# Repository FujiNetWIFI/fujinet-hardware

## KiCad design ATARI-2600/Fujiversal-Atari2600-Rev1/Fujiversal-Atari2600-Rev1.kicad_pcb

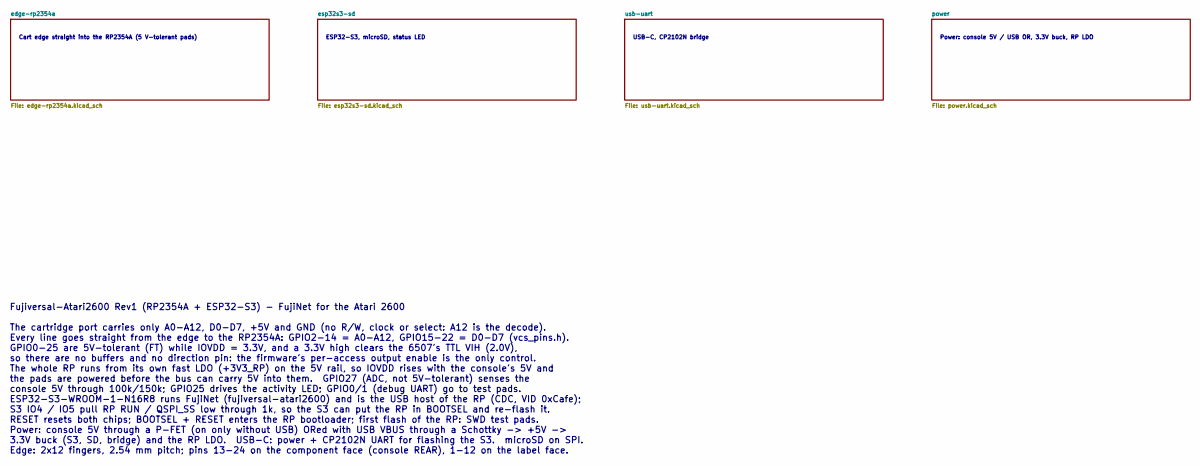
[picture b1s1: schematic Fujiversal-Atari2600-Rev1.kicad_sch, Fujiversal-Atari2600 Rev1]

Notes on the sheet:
Cart edge straight into the RP2354A (5 V-tolerant pads)
ESP32-S3, microSD, status LED
USB-C, CP2102N bridge
Power: console 5V / USB OR, 3.3V buck, RP LDO
Fujiversal-Atari2600 Rev1 (RP2354A + ESP32-S3) - FujiNet for the Atari 2600 The cartridge port carries only A0-A12, D0-D7, +5V and GND (no R/W, clock or select: A12 is the decode). Every line goes straight from the edge to the RP2354A: GPIO2-14 = A0-A12, GPIO15-22 = D0-D7 (vcs_pins.h). GPIO0-25 are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

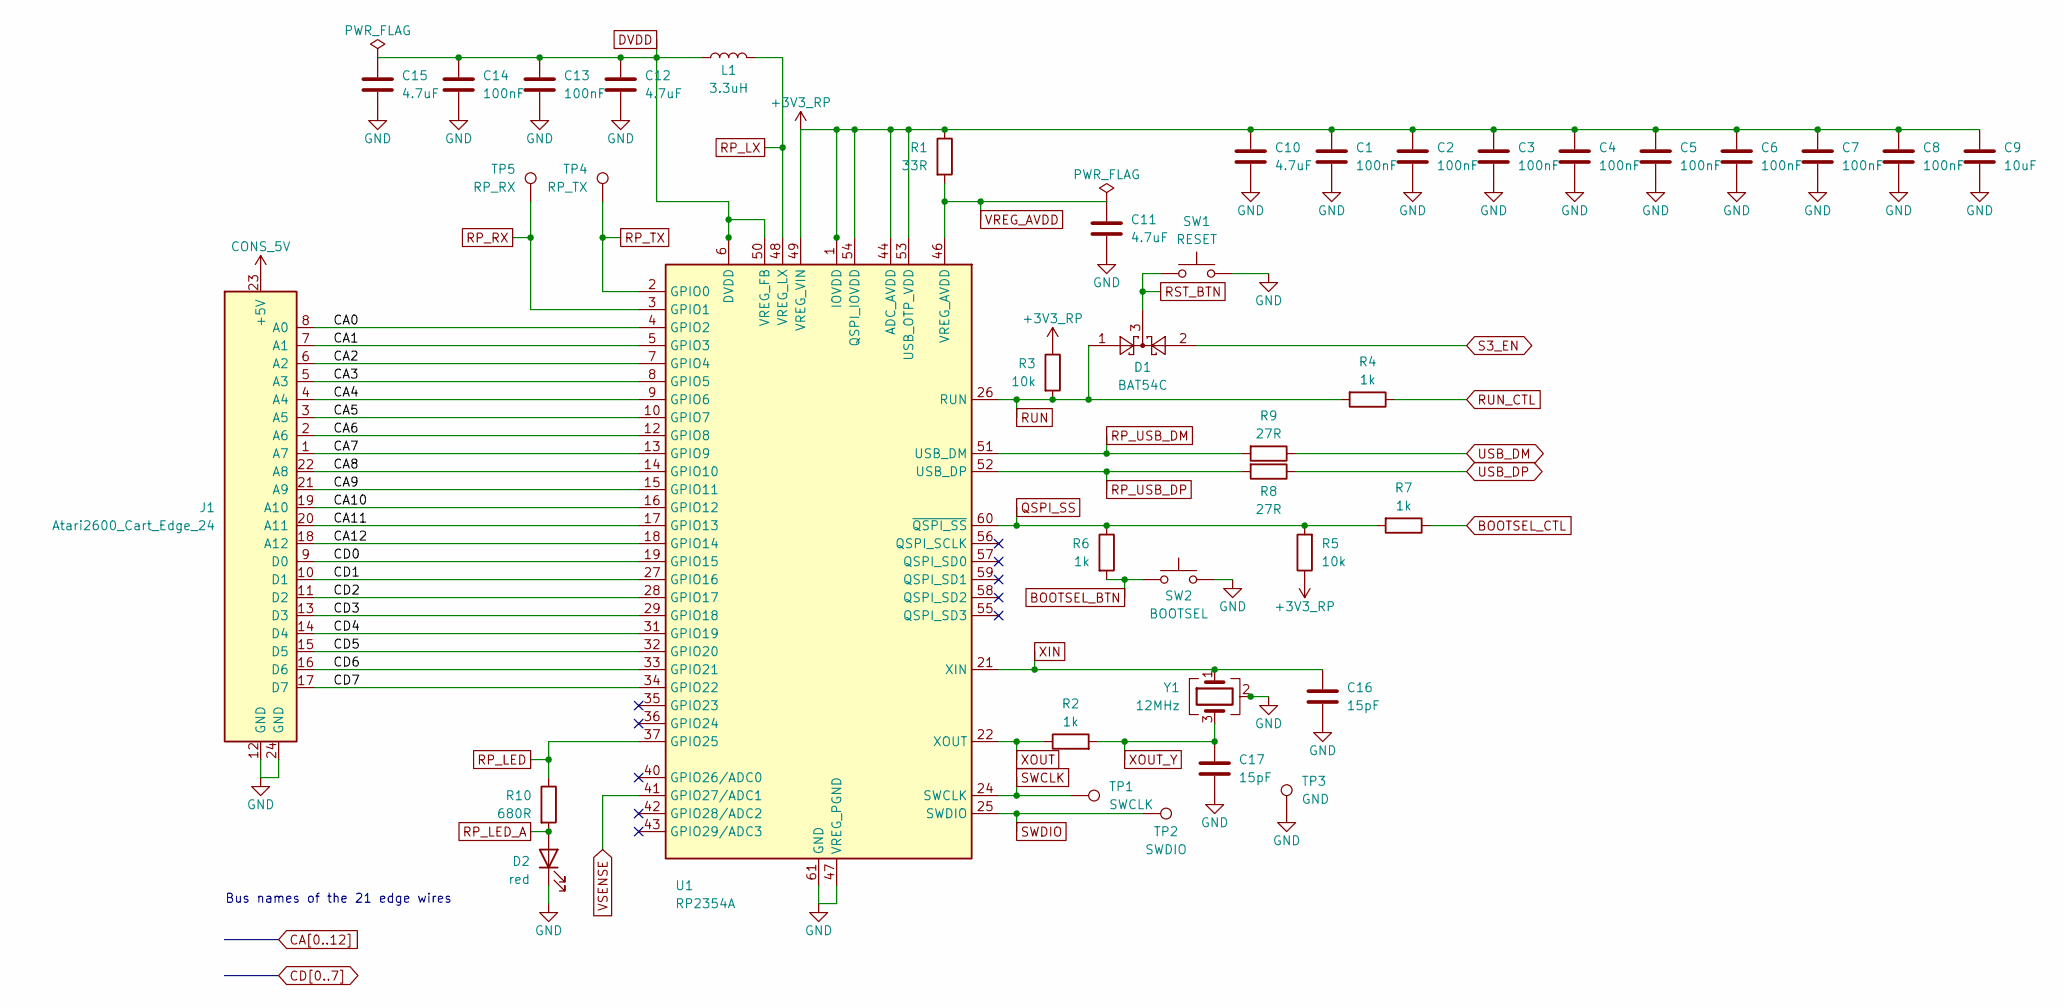
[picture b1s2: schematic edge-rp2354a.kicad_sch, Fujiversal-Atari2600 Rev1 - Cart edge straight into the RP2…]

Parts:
C1, C2, C3, C4, C5, C6, C7, C13, C14: 100nF; C_0603_1608Metric; MPN CC0603KRX7R9BB104; LCSC C14663
C8: 100nF; RPI_C0402; MPN CL05B104KO5NNNC; LCSC C1525
C9: 10uF; C_0603_1608Metric; MPN CL10A106KP8NNNC; LCSC C19702
C10, C12: 4.7uF; RPI_C0402_wide; MPN CL05A475MP5NRNC; LCSC C23733
C11: 4.7uF; RPI_C0402; MPN CL05A475MP5NRNC; LCSC C23733
C15: 4.7uF; C_0603_1608Metric; MPN CL10A475KO8NNNC; LCSC C19666
C16, C17: 15pF; C_0603_1608Metric; MPN CL10C150JB8NNNC; LCSC C1644
D1: BAT54C; SOT-23; MPN BAT54C,215; LCSC C37704
D2: red; LED_0603_1608Metric; MPN KT-0603R; LCSC C2286
J1: Atari2600_Cart_Edge_24
L1: 3.3uH; RPI_L_AOTA-B201610S3R3; MPN AOTA-B201610S3R3-101-T; LCSC C42411119
R1: 33R; RPI_R0402; MPN 0402WGF330JTCE; LCSC C25105
R2, R4, R6, R7: 1k; R_0603_1608Metric; MPN 0603WAF1001T5E; LCSC C21190
R3, R5: 10k; R_0603_1608Metric; MPN 0603WAF1002T5E; LCSC C25804
R8, R9: 27R; RPI_R0402; MPN 0402WGF270JTCE; LCSC C25100
R10: 680R; R_0603_1608Metric; MPN 0603WAF6800T5E; LCSC C23228
SW1: RESET; SW_SPST_TL3342; MPN TL3342F160QG; LCSC C2886898
SW2: BOOTSEL; SW_SPST_TL3342; MPN TL3342F160QG; LCSC C2886898
TP1: SWCLK; TestPoint_Pad_D1.5mm
TP2: SWDIO; TestPoint_Pad_D1.5mm
TP3: GND; TestPoint_Pad_D1.5mm
TP4: RP_TX; TestPoint_Pad_D1.5mm
TP5: RP_RX; TestPoint_Pad_D1.5mm
U1: RP2354A; RPI_RP2350A_QFN60; MPN RP2354A; LCSC C41378174
Y1: 12MHz; Crystal_SMD_3225-4Pin_3.2x2.5mm; MPN ABM8-272-T3; LCSC C20625731

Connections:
+3V3_RP: C1.1, C2.1, C3.1, C4.1, C5.1, C6.1, C7.1, C8.1, C9.1, C10.1, R1.1, R3.1, R5.1, U1.1 (IOVDD), U1.11 (IOVDD), U1.20 (IOVDD), U1.30 (IOVDD), U1.38 (IOVDD), U1.44 (ADC_AVDD), U1.45 (IOVDD), U1.49 (VREG_VIN), U1.53 (USB_OTP_VDD), U1.54 (QSPI_IOVDD); also elsewhere on the board
BOOTSEL_BTN: R6.2, SW2.1
BOOTSEL_CTL: R7.1; also elsewhere on the board
CA0: J1.8 (A0), U1.4 (GPIO2)
CA1: J1.7 (A1), U1.5 (GPIO3)
CA2: J1.6 (A2), U1.7 (GPIO4)
CA3: J1.5 (A3), U1.8 (GPIO5)
CA4: J1.4 (A4), U1.9 (GPIO6)
CA5: J1.3 (A5), U1.10 (GPIO7)
CA6: J1.2 (A6), U1.12 (GPIO8)
CA7: J1.1 (A7), U1.13 (GPIO9)
CA8: J1.22 (A8), U1.14 (GPIO10)
CA9: J1.21 (A9), U1.15 (GPIO11)
CA10: J1.19 (A10), U1.16 (GPIO12)
CA11: J1.20 (A11), U1.17 (GPIO13)
CA12: J1.18 (A12), U1.18 (GPIO14)
CD0: J1.9 (D0), U1.19 (GPIO15)
CD1: J1.10 (D1), U1.27 (GPIO16)
CD2: J1.11 (D2), U1.28 (GPIO17)
CD3: J1.13 (D3), U1.29 (GPIO18)
CD4: J1.14 (D4), U1.31 (GPIO19)
CD5: J1.15 (D5), U1.32 (GPIO20)
CD6: J1.16 (D6), U1.33 (GPIO21)
CD7: J1.17 (D7), U1.34 (GPIO22)
CONS_5V: J1.23 (+5V); also elsewhere on the board
DVDD: C12.1, C13.1, C14.1, C15.1, L1.1, U1.6 (DVDD), U1.23 (DVDD), U1.39 (DVDD), U1.50 (VREG_FB)
GND: C1.2, C2.2, C3.2, C4.2, C5.2, C6.2, C7.2, C8.2, C9.2, C10.2, C11.2, C12.2, C13.2, C14.2, C15.2, C16.2, C17.2, D2.1 (K), J1.12 (GND), J1.24 (GND), SW1.2, SW2.2, TP3.1, U1.47 (VREG_PGND), U1.61 (GND), Y1.2 (G), Y1.4 (G); also elsewhere on the board
QSPI_SS: R5.2, R6.1, R7.2, U1.60 (~QSPI_SS)
RP_LED: R10.1, U1.37 (GPIO25)
RP_LED_A: D2.2 (A), R10.2
RP_LX: L1.2, U1.48 (VREG_LX)
RP_RX: TP5.1, U1.3 (GPIO1)
RP_TX: TP4.1, U1.2 (GPIO0)
RP_USB_DM: R9.2, U1.51 (USB_DM)
RP_USB_DP: R8.2, U1.52 (USB_DP)
RST_BTN: D1.3, SW1.1
RUN: D1.1, R3.2, R4.2, U1.26 (RUN)
RUN_CTL: R4.1; also elsewhere on the board
S3_EN: D1.2; also elsewhere on the board
SWCLK: TP1.1, U1.24 (SWCLK)
SWDIO: TP2.1, U1.25 (SWDIO)
USB_DM: R9.1; also elsewhere on the board
USB_DP: R8.1; also elsewhere on the board
VREG_AVDD: C11.1, R1.2, U1.46 (VREG_AVDD)
VSENSE: U1.41 (GPIO27/ADC1); also elsewhere on the board
XIN: C16.1, U1.21 (XIN), Y1.1
XOUT: R2.1, U1.22 (XOUT)
XOUT_Y: C17.1, R2.2, Y1.3

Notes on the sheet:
Bus names of the 21 edge wires

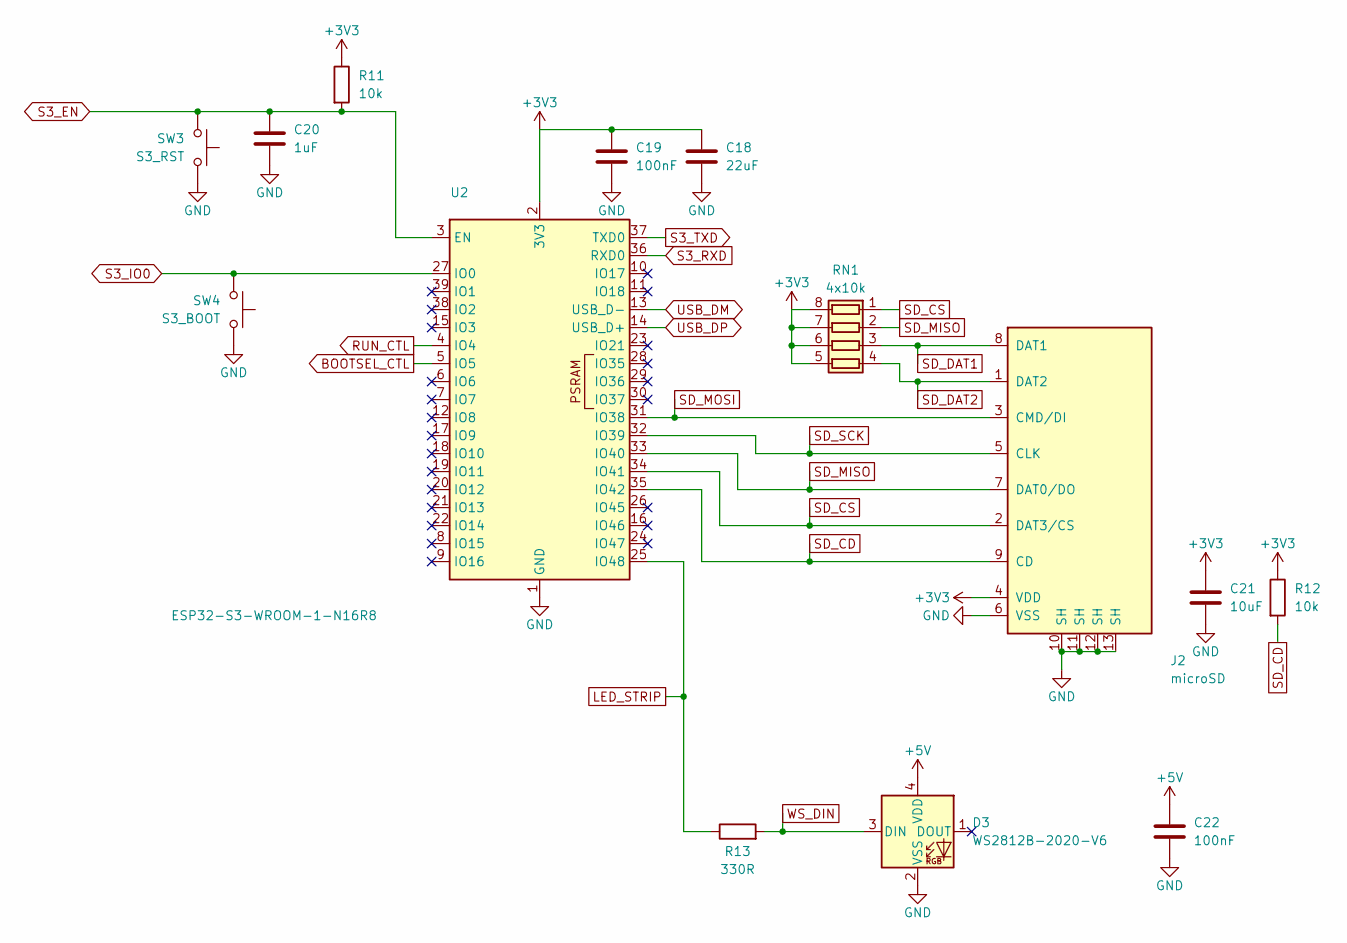
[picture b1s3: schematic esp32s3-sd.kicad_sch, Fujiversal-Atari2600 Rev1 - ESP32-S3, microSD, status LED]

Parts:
C18: 22uF; C_0805_2012Metric; MPN CL21A226MAQNNNE; LCSC C45783
C19, C22: 100nF; C_0603_1608Metric; MPN CC0603KRX7R9BB104; LCSC C14663
C20: 1uF; C_0603_1608Metric; MPN CL10A105KB8NNNC; LCSC C15849
C21: 10uF; C_0603_1608Metric; MPN CL10A106KP8NNNC; LCSC C19702
D3: WS2812B-2020-V6; LED_WS2812B-2020_PLCC4_2.0x2.0mm; MPN WS2812B-2020-V6; LCSC C52917434
J2: microSD; TF-SMD_TF-015; MPN TF-015; LCSC C113206
R11, R12: 10k; R_0603_1608Metric; MPN 0603WAF1002T5E; LCSC C25804
R13: 330R; R_0603_1608Metric; MPN 0603WAF3300T5E; LCSC C23138
RN1: 4x10k; R_Array_Convex_4x0603; MPN 4D03WGJ0103T5E; LCSC C29718
SW3: S3_RST; SW_SPST_TL3342; MPN TL3342F160QG; LCSC C2886898
SW4: S3_BOOT; SW_SPST_TL3342; MPN TL3342F160QG; LCSC C2886898
U2: ESP32-S3-WROOM-1-N16R8; ESP32-S3-WROOM-1; MPN ESP32-S3-WROOM-1-N16R8; LCSC C2913202

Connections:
+3V3: C18.1, C19.1, C21.1, J2.4 (VDD), R11.1, R12.1, RN1.5 (R4.2), RN1.6 (R3.2), RN1.7 (R2.2), RN1.8 (R1.2), U2.2 (3V3); also elsewhere on the board
+5V: C22.1, D3.4 (VDD); also elsewhere on the board
BOOTSEL_CTL: U2.5 (IO5); also elsewhere on the board
GND: C18.2, C19.2, C20.2, C21.2, C22.2, D3.2 (VSS), J2.6 (VSS), J2.10 (SH), J2.11 (SH), J2.12 (SH), J2.13 (SH), SW3.2, SW4.2, U2.1 (GND), U2.40 (GND), U2.41 (GND); also elsewhere on the board
LED_STRIP: R13.1, U2.25 (IO48)
RUN_CTL: U2.4 (IO4); also elsewhere on the board
S3_EN: C20.1, R11.2, SW3.1, U2.3 (EN); also elsewhere on the board
S3_IO0: SW4.1, U2.27 (IO0); also elsewhere on the board
S3_RXD: U2.36 (RXD0); also elsewhere on the board
S3_TXD: U2.37 (TXD0); also elsewhere on the board
SD_CD: J2.9 (CD), R12.2, U2.35 (IO42)
SD_CS: J2.2 (DAT3/CS), RN1.1 (R1.1), U2.34 (IO41)
SD_DAT1: J2.8 (DAT1), RN1.3 (R3.1)
SD_DAT2: J2.1 (DAT2), RN1.4 (R4.1)
SD_MISO: J2.7 (DAT0/DO), RN1.2 (R2.1), U2.33 (IO40)
SD_MOSI: J2.3 (CMD/DI), U2.31 (IO38)
SD_SCK: J2.5 (CLK), U2.32 (IO39)
USB_DM: U2.13 (USB_D-); also elsewhere on the board
USB_DP: U2.14 (USB_D+); also elsewhere on the board
WS_DIN: D3.3 (DIN), R13.2

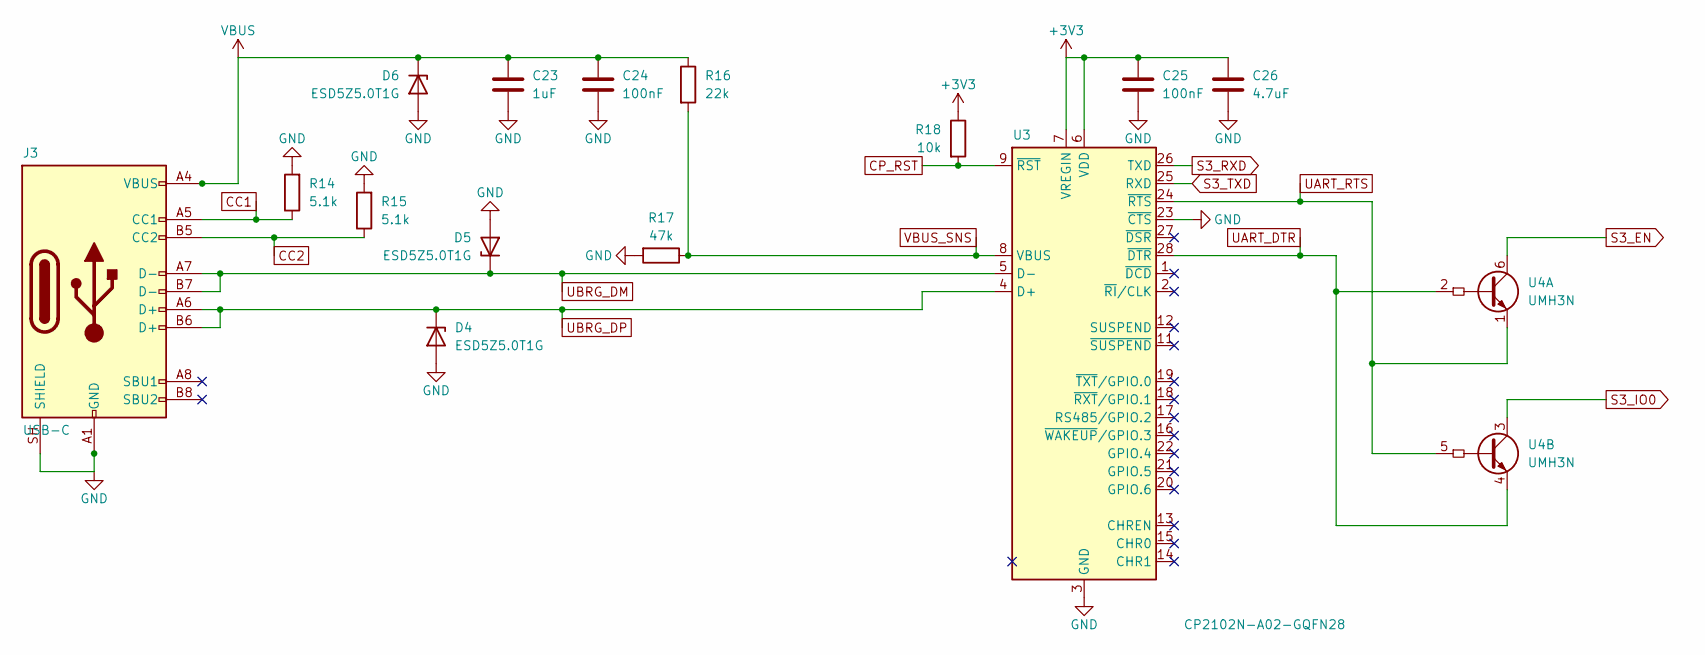
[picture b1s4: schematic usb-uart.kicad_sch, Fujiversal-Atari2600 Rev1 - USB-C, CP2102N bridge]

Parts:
C23: 1uF; C_0603_1608Metric; MPN CL10A105KB8NNNC; LCSC C15849
C24, C25: 100nF; C_0603_1608Metric; MPN CC0603KRX7R9BB104; LCSC C14663
C26: 4.7uF; C_0603_1608Metric; MPN CL10A475KO8NNNC; LCSC C19666
D4, D5, D6: ESD5Z5.0T1G; D_SOD-523; MPN ESD5Z5.0T1G; LCSC C82044
J3: USB-C; USB_C_Receptacle_HRO_TYPE-C-31-M-12; MPN TYPE-C-31-M-12; LCSC C165948
R14, R15: 5.1k; R_0603_1608Metric; MPN 0603WAF5101T5E; LCSC C23186
R16: 22k; R_0603_1608Metric; MPN 0603WAF2202T5E; LCSC C31850
R17: 47k; R_0603_1608Metric; MPN 0603WAF4702T5E; LCSC C25819
R18: 10k; R_0603_1608Metric; MPN 0603WAF1002T5E; LCSC C25804
U3: CP2102N-A02-GQFN28; QFN-28-1EP_5x5mm_P0.5mm_EP3.35x3.35mm; MPN CP2102N-A02-GQFN28R; LCSC C964632
U4: UMH3N; SOT-363_SC-70-6; MPN UMH3N; LCSC C62892

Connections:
+3V3: C25.1, C26.1, R18.1, U3.6 (VDD), U3.7 (VREGIN); also elsewhere on the board
CC1: J3.A5 (CC1), R14.1
CC2: J3.B5 (CC2), R15.1
CP_RST: R18.2, U3.9 (~RST)
GND: C23.2, C24.2, C25.2, C26.2, D4.2 (A), D5.2 (A), D6.2 (A), J3.A1 (GND), J3.A12 (GND), J3.B1 (GND), J3.B12 (GND), J3.SH (SHIELD), R14.2, R15.2, R17.2, U3.3 (GND), U3.23 (~CTS), U3.29 (GND); also elsewhere on the board
S3_EN: U4.6 (C1); also elsewhere on the board
S3_IO0: U4.3 (C2); also elsewhere on the board
S3_RXD: U3.26 (TXD); also elsewhere on the board
S3_TXD: U3.25 (RXD); also elsewhere on the board
UART_DTR: U3.28 (~DTR), U4.2 (B1), U4.4 (E2)
UART_RTS: U3.24 (~RTS), U4.1 (E1), U4.5 (B2)
UBRG_DM: D5.1 (K), J3.A7 (D-), J3.B7 (D-), U3.5 (D-)
UBRG_DP: D4.1 (K), J3.A6 (D+), J3.B6 (D+), U3.4 (D+)
VBUS: C23.1, C24.1, D6.1 (K), J3.A4 (VBUS), J3.A9 (VBUS), J3.B4 (VBUS), J3.B9 (VBUS), R16.1; also elsewhere on the board
VBUS_SNS: R16.2, R17.1, U3.8 (VBUS)

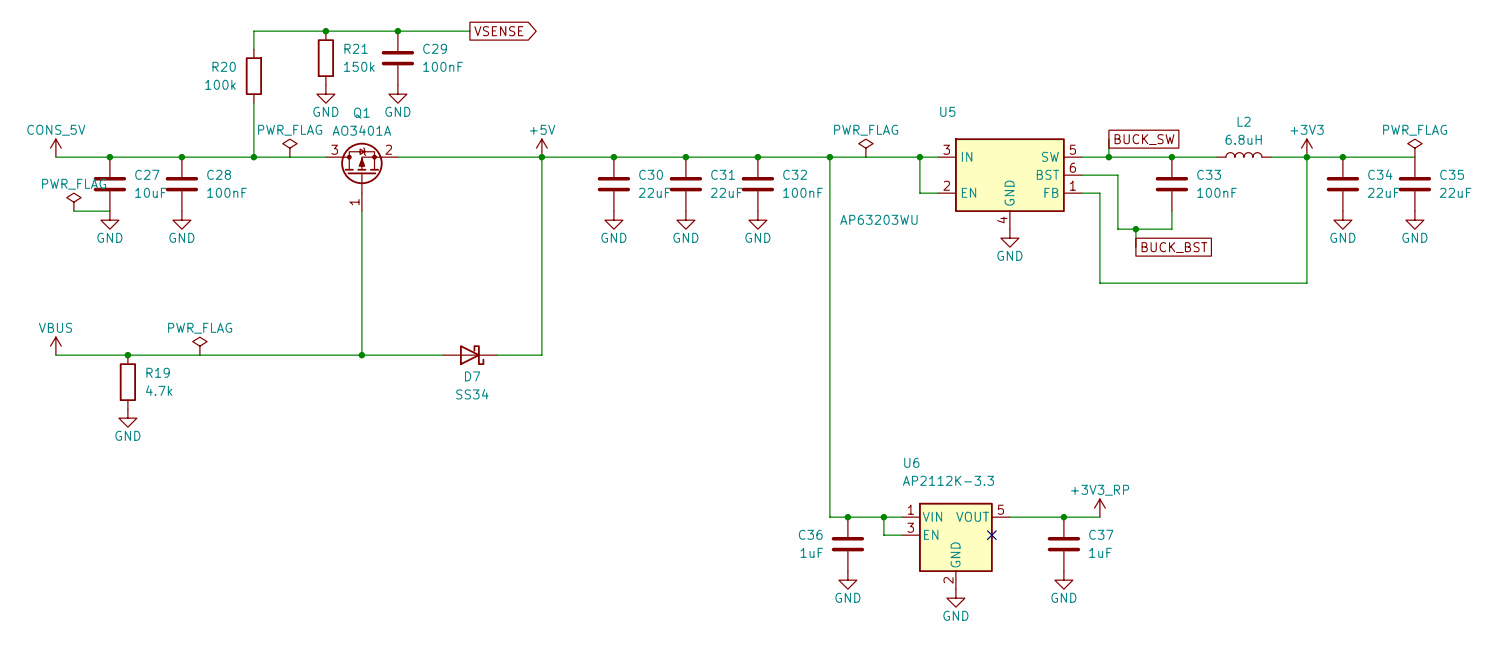
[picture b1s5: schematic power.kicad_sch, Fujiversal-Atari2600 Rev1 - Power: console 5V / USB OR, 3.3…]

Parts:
C27: 10uF; C_0603_1608Metric; MPN CL10A106KP8NNNC; LCSC C19702
C28, C29, C32, C33: 100nF; C_0603_1608Metric; MPN CC0603KRX7R9BB104; LCSC C14663
C30, C31, C34, C35: 22uF; C_0805_2012Metric; MPN CL21A226MAQNNNE; LCSC C45783
C36, C37: 1uF; C_0603_1608Metric; MPN CL10A105KB8NNNC; LCSC C15849
D7: SS34; D_SMA; MPN SS34; LCSC C8678
L2: 6.8uH; L_Sunlord_SWPA4030S; MPN SWPA4030S6R8MT; LCSC C62684
Q1: AO3401A; SOT-23; MPN AO3401A; LCSC C15127
R19: 4.7k; R_0603_1608Metric; MPN 0603WAF4701T5E; LCSC C23162
R20: 100k; R_0603_1608Metric; MPN 0603WAF1003T5E; LCSC C25803
R21: 150k; R_0603_1608Metric; MPN 0603WAF1503T5E; LCSC C22807
U5: AP63203WU; TSOT-23-6; MPN AP63203WU-7; LCSC C780769
U6: AP2112K-3.3; SOT-23-5; MPN AP2112K-3.3TRG1; LCSC C51118

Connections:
+3V3: C34.1, C35.1, L2.2, U5.1 (FB); also elsewhere on the board
+3V3_RP: C37.1, U6.5 (VOUT); also elsewhere on the board
+5V: C30.1, C31.1, C32.1, C36.1, D7.1 (K), Q1.2 (S), U5.2 (EN), U5.3 (IN), U6.1 (VIN), U6.3 (EN); also elsewhere on the board
BUCK_BST: C33.2, U5.6 (BST)
BUCK_SW: C33.1, L2.1, U5.5 (SW)
CONS_5V: C27.1, C28.1, Q1.3 (D), R20.1; also elsewhere on the board
GND: C27.2, C28.2, C29.2, C30.2, C31.2, C32.2, C34.2, C35.2, C36.2, C37.2, R19.2, R21.2, U5.4 (GND), U6.2 (GND); also elsewhere on the board
VBUS: D7.2 (A), Q1.1 (G), R19.1; also elsewhere on the board
VSENSE: C29.1, R20.2, R21.1; also elsewhere on the board

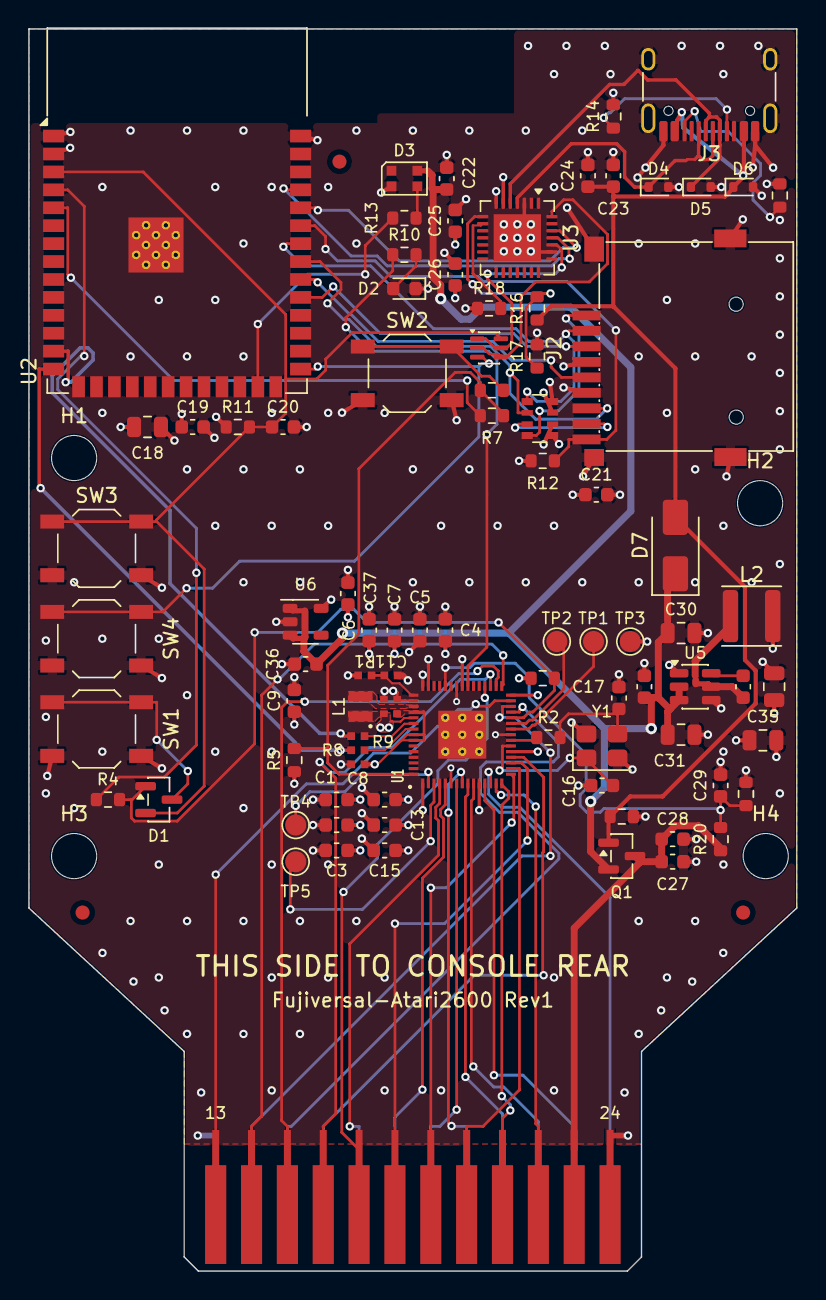
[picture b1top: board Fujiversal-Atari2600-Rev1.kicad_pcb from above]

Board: 4 copper layers, 54.4 x 88.0 mm, 95 parts (0 on the bottom side), 73 nets.

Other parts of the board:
FID1, FID2, FID3: Fiducial_1mm_Mask2mm
H1, H2, H3, H4: MountingHole_3.2mm_NPTH

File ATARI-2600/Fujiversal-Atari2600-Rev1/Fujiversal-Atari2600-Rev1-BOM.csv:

"Refs","Value","Footprint","MPN","LCSC","Description","DNP"
"C1,C2,C3,C4,C5,C6,C7,C13,C14,C19,C22,C24,C25,C28,C29,C32,C33","100nF","C_0603_1608Metric","CC0603KRX7R9BB104","C14663","IOVDD decoupling (pin 1)",""
"C8","100nF","RPI_C0402","CL05B104KO5NNNC","C1525","USB_OTP_VDD + QSPI_IOVDD decoupling",""
"C9,C21,C27","10uF","C_0603_1608Metric","CL10A106KP8NNNC","C19702","+3V3_RP bulk at the RP",""
"C10,C12","4.7uF","RPI_C0402_wide","CL05A475MP5NRNC","C23733","VREG_VIN input (C_IN)",""
"C11","4.7uF","RPI_C0402","CL05A475MP5NRNC","C23733","VREG_AVDD RC filter (C_FILT)",""
"C15,C26","4.7uF","C_0603_1608Metric","CL10A475KO8NNNC","C19666","DVDD decoupling (pin 23, far from the regulator)",""
"C16,C17","15pF","C_0603_1608Metric","CL10C150JB8NNNC","C1644","crystal load",""
"C18,C30,C31,C34,C35","22uF","C_0805_2012Metric","CL21A226MAQNNNE","C45783","S3 bulk (WiFi TX bursts)",""
"C20,C23,C36,C37","1uF","C_0603_1608Metric","CL10A105KB8NNNC","C15849","EN power-on delay",""
"D1","BAT54C","SOT-23","BAT54C,215","C37704","RESET steering, common cathode",""
"D2","red","LED_0603_1608Metric","KT-0603R","C2286","RP activity LED (GP25)",""
"D3","WS2812B-2020-V6","LED_WS2812B-2020_PLCC4_2.0x2.0mm","WS2812B-2020-V6","C52917434","status LED on +5V",""
"D4,D5,D6","ESD5Z5.0T1G","D_SOD-523","ESD5Z5.0T1G","C82044","ESD",""
"D7","SS34","D_SMA","SS34","C8678","USB VBUS OR-ing (no back-feed into the console)",""
"J2","microSD","TF-SMD_TF-015","TF-015","C113206","microSD push-push, SPI mode",""
"J3","USB-C","USB_C_Receptacle_HRO_TYPE-C-31-M-12","TYPE-C-31-M-12","C165948","power + S3 programming",""
"L1","3.3uH","RPI_L_AOTA-B201610S3R3","AOTA-B201610S3R3-101-T","C42411119","RP2350 core SMPS inductor (polarity marked)",""
"L2","6.8uH","L_Sunlord_SWPA4030S","SWPA4030S6R8MT","C62684","buck inductor",""
"Q1","AO3401A","SOT-23","AO3401A","C15127","console 5V switch: G = VBUS, S = +5V, D = CONS_5V; body diode CONS_5V -> +5V",""
"R1","33R","RPI_R0402","0402WGF330JTCE","C25105","VREG_AVDD RC filter (R_FILT)",""
"R2,R4,R6,R7","1k","R_0603_1608Metric","0603WAF1001T5E","C21190","crystal drive limit",""
"R3,R5,R11,R12,R18","10k","R_0603_1608Metric","0603WAF1002T5E","C25804","RUN pull-up",""
"R8,R9","27R","RPI_R0402","0402WGF270JTCE","C25100","USB series",""
"R10","680R","R_0603_1608Metric","0603WAF6800T5E","C23228","LED series (~2 mA)",""
"R13","330R","R_0603_1608Metric","0603WAF3300T5E","C23138","WS2812 data series",""
"R14,R15","5.1k","R_0603_1608Metric","0603WAF5101T5E","C23186","UFP Rd",""
"R16","22k","R_0603_1608Metric","0603WAF2202T5E","C31850","VBUS sense divider",""
"R17","47k","R_0603_1608Metric","0603WAF4702T5E","C25819","VBUS sense divider",""
"R19","4.7k","R_0603_1608Metric","0603WAF4701T5E","C23162","P-FET gate pull-down against the SS34 reverse leakage",""
"R20","100k","R_0603_1608Metric","0603WAF1003T5E","C25803","console 5V sense divider",""
"R21","150k","R_0603_1608Metric","0603WAF1503T5E","C22807","console 5V sense divider (0.6 x CONS_5V)",""
"RN1","4x10k","R_Array_Convex_4x0603","4D03WGJ0103T5E","C29718","SD pull-ups",""
"SW1","RESET","SW_SPST_TL3342","TL3342F160QG","C2886898","cart RESET: RP RUN + S3 EN through the BAT54C",""
"SW2","BOOTSEL","SW_SPST_TL3342","TL3342F160QG","C2886898","RP2354A BOOTSEL (hold while pressing RESET)",""
"SW3","S3_RST","SW_SPST_TL3342","TL3342F160QG","C2886898","ESP32-S3 EN",""
"SW4","S3_BOOT","SW_SPST_TL3342","TL3342F160QG","C2886898","ESP32-S3 BOOT (IO0)",""
"U1","RP2354A","RPI_RP2350A_QFN60","RP2354A","C41378174","RP2350A + 2MB flash in package; serves the 2600 cart bus",""
"U2","ESP32-S3-WROOM-1-N16R8","ESP32-S3-WROOM-1","ESP32-S3-WROOM-1-N16R8","C2913202","FujiNet core (fujiversal-atari2600)",""
"U3","CP2102N-A02-GQFN28","QFN-28-1EP_5x5mm_P0.5mm_EP3.35x3.35mm","CP2102N-A02-GQFN28R","C964632","USB-UART for S3 flashing/console (self-powered)",""
"U4","UMH3N","SOT-363_SC-70-6","UMH3N","C62892","esptool auto-program (DevKitC-1 style)",""
"U5","AP63203WU","TSOT-23-6","AP63203WU-7","C780769","3.3V 2A buck (S3, SD, CP2102N)",""
"U6","AP2112K-3.3","SOT-23-5","AP2112K-3.3TRG1","C51118","RP2354A 3.3V LDO (IOVDD, VREG_VIN, VREG_AVDD), 600mA, fast start",""
"Y1","12MHz","Crystal_SMD_3225-4Pin_3.2x2.5mm","ABM8-272-T3","C20625731","",""

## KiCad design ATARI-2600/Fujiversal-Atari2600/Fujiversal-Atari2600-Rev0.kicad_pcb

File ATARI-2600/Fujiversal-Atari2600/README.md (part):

# Fujiversal-Atari2600 Rev0

All-in-one **Atari 2600 FujiNet cartridge**. It is the hardware for the Atari
2600 bring-up in fujinet-firmware (branch `2600-experiment`,
`pico/atari-2600/`). It uses the same two-chip architecture as INTV Rev0 and
Astrocade Rev0.

- **RP2040** + **W25Q16JV (2 MB)** runs the cart firmware built as board
  **`fujivcs`**. The pinout is exactly `include/vcs_pins.h`, so the firmware
  runs unchanged. The RP2040 is not 5 V tolerant, so every bus line goes
  through a **74LVC245A** powered at 3.3 V:
  - **U3** carries A0-A7 and **U4** carries A8-A12, both fixed A→B.
  - **U5** carries D0-D7. Its DIR pin is on GP26 and is pulled high.
- **ESP32-S3-WROOM-1-N16R8** runs the **`fujiversal-atari2600`** build of
  fujinet-firmware. It is the RP's USB *host*: S3 IO19/IO20 connect through
  27 R to the RP's USB, and the RP enumerates as a CDC device with VID
  0xCafe. There is no UART between the two chips.
- **USB-C** provides power and a CP2102N UART with UMH3N auto-program for
  flashing the S3.
- **microSD** is push-push, on SPI (IO38-41), with card-detect on IO42.
- **WS2812B-2020-V6** status LED (IO48), plus a green RP activity LED on GP25.
- **Buttons:**
  - **RESET** resets both chips. This is how you get back to the browser
    after booting a game (`main.c`: "an item for the PCB").
  - **BOOTSEL** for the RP2040.
  - S3 **EN** and S3 **BOOT**.
- The S3 can also force the RP into reset or BOOTSEL with IO4 → RUN and
  IO5 → QSPI_SS, active low through 1k, as on the INTV and Astrocade boards.

The board is a **4-layer**, **fully autorouted** design, with a printed
two-piece shell. Everything is generated from `tools/design.py` and
`tools/placement.py`: edit those, never the KiCad files (see *Regenerating*).

## Edge connector

2x12 gold fingers at 2.54 mm pitch, 1.5 x 7.0 mm, starting 0.5 mm from the
edge.

- **Tab:** 32.4 mm wide, with 45° shoulders reaching the full 54.4 mm width
  25.7 mm above the edge.
- **Geometry and orientation:** taken from the working FujiPlusCart prototype
  gerbers (`../FujiPlusCart-Prototype`). Its silkscreen reads "THIS SIDE TO
  CONSOLE REAR" on the component face.

| Face | Fingers, left → right (component face toward you) |
|---|---|
| **F.Cu** (components, console **rear**) | 13 D3, 14 D4, 15 D5, 16 D6, 17 D7, 18 A12, 19 A10, 20 A11, 21 A9, 22 A8, 23 +5V, 24 GND |
| **B.Cu** (label side, console **front**) | 12 GND, 11 D2, 10 D1, 9 D0, 8 A0, 7 A1, 6 A2, 5 A3, 4 A4, 3 A5, 2 A6, 1 A7 (pin 1 is behind pin 24) |

**Signals the edge does not carry:** R/W, clock, chip select (A12 is the only
decode) and reset.

**The RP pin map** (`vcs_pins.h`, checked by `tools/check_nets.py`):

| RP2040 | Net | Through |
|---|---|---|
| GP2-GP9 | RA0-RA7 | U3 (74LVC245A, DIR = H) ← CA0-CA7 |
| GP10-GP14 | RA8-RA12 | U4 (DIR = H; channels 5-7 unused, inputs grounded) ← CA8-CA12 |
| GP15-GP22 | RD0-RD7 | U5 ↔ CD0-CD7 |
| GP26 | BUF_DIR | U5 DIR, with a 10k pull-up |
| GP25 | RP_LED | green LED (`PICO_DEFAULT_LED_PIN`) |
| GP0 / GP1 | RP_TX / RP_RX | test pads TP4 / TP5 |
| SWCLK / SWDIO | | test pads TP1 / TP2, GND on TP3 |

**Why 74LVC245A and not the 74LVC8T245 named in the firmware.**

- **74LVC8T245:** its DIR pin is referenced to VCCA.
  - With the 5 V port as A, a 3.3 V GPIO can't reach VIH on DIR.
  - With the 3.3 V port as A, the polarity inverts relative to
    `DIR_PIN: 0 = cart drives the console`.
- **74LVC245A at 3.3 V:**
  - It tolerates 5 V on its inputs, and it has Ioff, so it is safe unpowered.
  - Its 3.3 V outputs clear the NMOS bus's TTL VIH (2.0 V), as PlusCart
    already relies on.
  - With A on the console, **DIR high = console → RP** (the boot value) and
    **DIR low = RP → console**.
  - Nothing on the board runs from the edge +5 V except the power diode, so
    the cart can't back-power a switched-off console through the bus.

> **Firmware item before bring-up:** nothing in the cart firmware drives
> DIR low yet. `main.c` sets GP26 = 1 at boot, and
> `DATA_DRIVE`/`DATA_RELEASE` in `vcs_pins.h` only toggle the RP's output
> enables. As written, the cart can't reach the console, and the RP would
> fight U5's B outputs whenever it drives.
>
> **Fix:** `DATA_DRIVE` must also clear `DIR_MASK`, and `DATA_RELEASE` must
> set it again (release the OEs first, then flip DIR). The '245 needs about
> 5-8 ns to turn around. This is noted in `README-fujinet.md` on the
> firmware side.

## Mechanics

**Board:** 54.4 x 88 mm, 1.6 mm thick. Every part sits on the component face,
above the shoulders; `gen_pcb.py` refuses a placement that breaks this.

**What goes into the console:** only the tab and shoulders, as with the
prototype.

**Finger strip:**
- It is a rule area on both faces: no tracks, vias or pour between the
  fingers.
- Each finger continues as a masked 0.5 mm neck to 10 mm from the edge,
  where the routers pick it up.
- The inner planes stop 9 mm from the edge, clear of the bevel.

**Top edge (y = 30):**
- USB-C and the microSD slot exit here.
- The ESP32-S3 antenna overhangs by 6.4 mm, into the shell's antenna pocket.

**Holes:** 4x M3 NPTH for the shell.

**Shell:** `case/`, see `case/case-spec.md`. It is a two-piece clamshell over
the full-width part of the board, 58 x 71 x 10 mm, with 4x M3 screws.

## Power

- **Sources:** console +5V (edge pin 23) and USB VBUS, each through an SS34
  (diode OR, so there is no back-feed between them) into VIN.
- **Regulation:** VIN feeds an AP63203 3.3 V/2 A buck (6.8 uH, 2x22 uF in,
  2x22 uF out).
- **RP2040 core:** 1.1 V from its internal LDO.
- **Decoupling:**
  - 100 nF on every IOVDD, USB_VDD, ADC_AVDD and DVDD pin
  - 1 uF on VREG_VIN and VREG_VOUT
  - 10 uF bulk each on 3V3 and at the edge +5V
- **Console budget:** the 2600 supplies +5V from its own 7805 fed by a 9 V
  adapter. At the 3.3 V rail this board should draw on the order of 60 mA
  idle and up to about 350 mA during WiFi TX bursts (estimated from the
  ESP32-S3 datasheet, not measured). Through the buck that is roughly
  250 mA peak from +5V.
  - The prototype (ESP32 DevKitC + Pico, all linear) ran on the same supply.
  - Still, measure the console's 5 V under WiFi load before trusting a
    2600 Jr (see the checklist).

## Flashing

- **ESP32-S3:** plug in the USB-C port (CP2102N, esptool auto-program) and run
  `pio run -e fujiversal-atari2600 -t upload`.
- **RP2040, first time:** the RP's USB goes only to the S3, so a PC can't
  see it as a UF2 drive. Use the SWD pads TP1 SWCLK, TP2 SWDIO and TP3 GND
  with a Raspberry Pi Debug Probe:
  `openocd -f interface/cmsis-dap.cfg -f target/rp2040.cfg -c "adapter speed 5000; program fujivcs.elf verify reset exit"`.
- **RP2040, afterwards:**
  - The mailbox BOOTSEL doorbell (`FN_REG_BOOTSEL_1/2`) puts the RP into
    BOOTSEL on the S3's USB.
  - So does holding **BOOTSEL** while pressing **RESET**.
  - So does IO5 held low across an IO4 pulse, which is `PIN_RP2040_BOOTSEL`
    / `PIN_RP2040_RUN`, as fnPicoUpdater expects.
  - A PICOBOOT client on the S3, as fujiversal-intv/-astrocade have, can
    then write the image. That client isn't on `2600-experiment` yet.

## Regenerating

**Requirements:**
- KiCad 10.0.6, Python 3, Java 21+
- Freerouting 2.4.1 at `~/.local/share/freerouting/freerouting-2.4.1.jar`
- the firmware tree at `~/Workspace/fn-2600` (or `$FUJINET_FIRMWARE`), for
  `check_nets.py`

`tools/build_all.sh` runs the whole chain (about 20 minutes):

```sh
python3 tools/make_edge_fp.py   # 2x12 finger footprint (both faces, masked necks)
python3 tools/gen_sch.py        # design.py -> root + 5 sheets, project symbol lib
python3 tools/gen_pcb.py        # placement + nets (from the schematic netlist) + locked plane fan-out,
                                # outline/tab, finger rule areas, planes, rules/net classes, case anchors,
                                # drawn DVDD ring / RP USB pair / GND-finger vias
python3 tools/finish_route.py --nets=DVDD,XIN,XOUT,XOUT_Y --lock   # core supply + crystal first, locked
python3 tools/route.py          # DSN -> Freerouting (headless) -> SES -> GND pours -> zone fill
python3 tools/finish_route.py   # grid A* (+ transactional rip-up) for anything left
python3 tools/tidy_tracks.py    # drop router crumbs, merge collinear runs, fix acute corners (DRC-checked)
python3 tools/set_models.py     # bundle-relative 3D models on every footprint
python3 tools/check_nets.py     # netlist vs the firmware headers (independent of design.py)
python3 tools/export.py         # BOM, JLCPCB BOM + CPL, gerbers/drill zip, schematic PDF, SVGs, renders
```

**Helper scripts:**

| Script | Purpose |
|---|---|
| `tools/lcsc.py` | Checks LCSC codes; `--search` queries JLCPCB's parts search |
| `tools/make_tf015_fp.py` | Rebuilds the microSD footprint from the EasyEDA export of C113206 |

**Toolchain origin:** the pipeline comes from `Astrocade/rev0`, without the
RP2350 regulator graft. That includes the S-expression board writer (pcbnew's
SWIG bindings are unreliable on Python 3.14), the locked plane fan-out with
1.2 mm escape lanes in front of fine-pitch pins, Freerouting, and the A*
finisher.

**How the bus is ordered.** The RP2040 is rotated 90°, so A0-A9 sit on its
south face directly above U3, and U3 sits directly above the B.Cu A0-A7
fingers, in the same order. The RP's other faces:
- **east:** A10-A12 (from U4, which sits south-east over the F.Cu A8-A12
  fingers), D0-D2 and the crystal
- **north:** D3-D7
- **west:** USB and QSPI, facing the S3 and the flash

U5 sits over the data fingers.

## Status

Rev0, generated 2026-09-27: schematic, 4-layer layout, **100% routed**,
fabrication outputs exported. **The board has not been built or tested on
hardware.**

| Check | Result |
|---|---|
| ERC (`--severity-all`) | 0 violations |
| DRC (`--schematic-parity`) | 0 errors, 0 unconnected, 0 parity. 81 warnings, all silkscreen cosmetics (reference text over copper or overlapping at 0603 density; silk over pads is clipped by the mask in the gerbers) |
| `tools/check_nets.py` | 355 of 355 checks pass. It reads `vcs_pins.h`, `fujivcs.cmake`/`fujivcs.h` and `fujiversal-atari2600.h` directly and traces every edge pin through its '245 to the right GPIO. It also checks DIR, /OE, the unused-input ties, the QSPI flash, the USB link, RUN/BOOTSEL, SD, LED and UART. A mutation test (D0_PIN 15 → 16, SD CS 41 → 42) fails 9 checks as it should |
| 3D | Every placed part has a bundled model (`docs/board-top.png`, `docs/board-bottom.png`) |
| Firmware | `pico/atari-2600/build-cart.sh` builds `fujivcs.uf2`, and `checksram` confirms core1 is SRAM-resident. `pio` env `fujiversal-atari2600` builds with the updated pinmap. The env needs a `data/webui/config/fujiversal-atari2600.yaml`, which is missing on `2600-experiment`; the build was verified with a temporary copy of the Astrocade one |
| Shell | Both halves render in OpenSCAD as 2-manifold (`Simple: yes`) |
| LCSC | Every code was checked with `tools/lcsc.py` against LCSC and JLC. All resolve to the part named, and all are in JLC stock |

**Routing notes.** Three spots were drawn as locked geometry in
`gen_pcb.py` rather than left to the routers, because a greedy router
always blocked one of the two lines:

- **DVDD** (`rp_dvdd_link`): VREG_VOUT pin 45 → DVDD pins 50 and 23, routed
  inside the RP2040's pin ring between the pads and the exposed pad, as
  Raspberry Pi's minimal design does.
- **The RP↔S3 USB pair** (`rp_usb_link`): pins 46/47 → R8/R7, down a
  via-free lane (`VIA_KEEP`).
- **The two GND fingers:** each is stitched to the In1 plane by a via 1.27 mm
  outboard of its neck. The fingers are back to back, so a via on the neck
  would short the finger behind it.

**Fab (JLCPCB):**

- **Board:** 4-layer, 1.6 mm, ENIG.
- **Gold fingers:** yes. **Bevel:** 30° on the insertion edge. Copper stops
  0.5 mm short of the edge, and the inner planes 9 mm short.
- **Limits used:** 0.15 mm clearance and track minimum, 0.3 mm minimum drill.
  This is standard 4-layer process.
- **Vias in pads:** the via arrays in the RP2040, CP2102N and ESP32-S3
  exposed pads are via-in-pad. Order "epoxy filled & capped" if it's
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
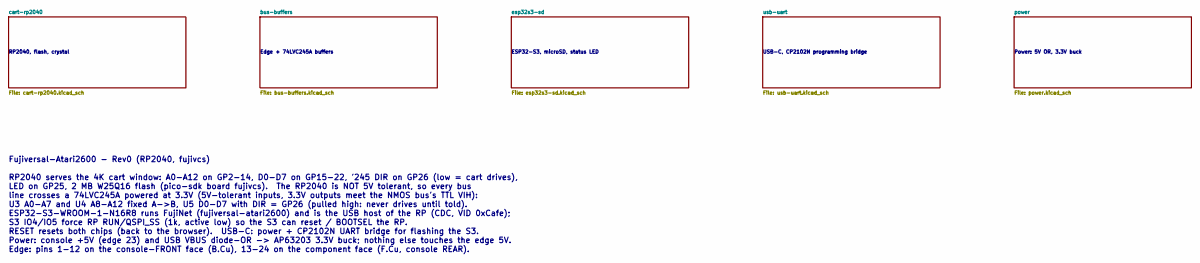
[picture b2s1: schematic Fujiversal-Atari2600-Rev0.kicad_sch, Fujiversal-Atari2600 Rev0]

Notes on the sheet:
RP2040, flash, crystal
Edge + 74LVC245A buffers
ESP32-S3, microSD, status LED
USB-C, CP2102N programming bridge
Power: 5V OR, 3.3V buck
Fujiversal-Atari2600 - Rev0 (RP2040, fujivcs) RP2040 serves the 4K cart window: A0-A12 on GP2-14, D0-D7 on GP15-22, '245 DIR on GP26 (low = cart drives), LED on GP25, 2 MB W25Q16 flash (pico-sdk board fujivcs). The RP2040 is NOT 5V tolerant, so every bus line crosses a 74LVC245A powered at 3.3V (5V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

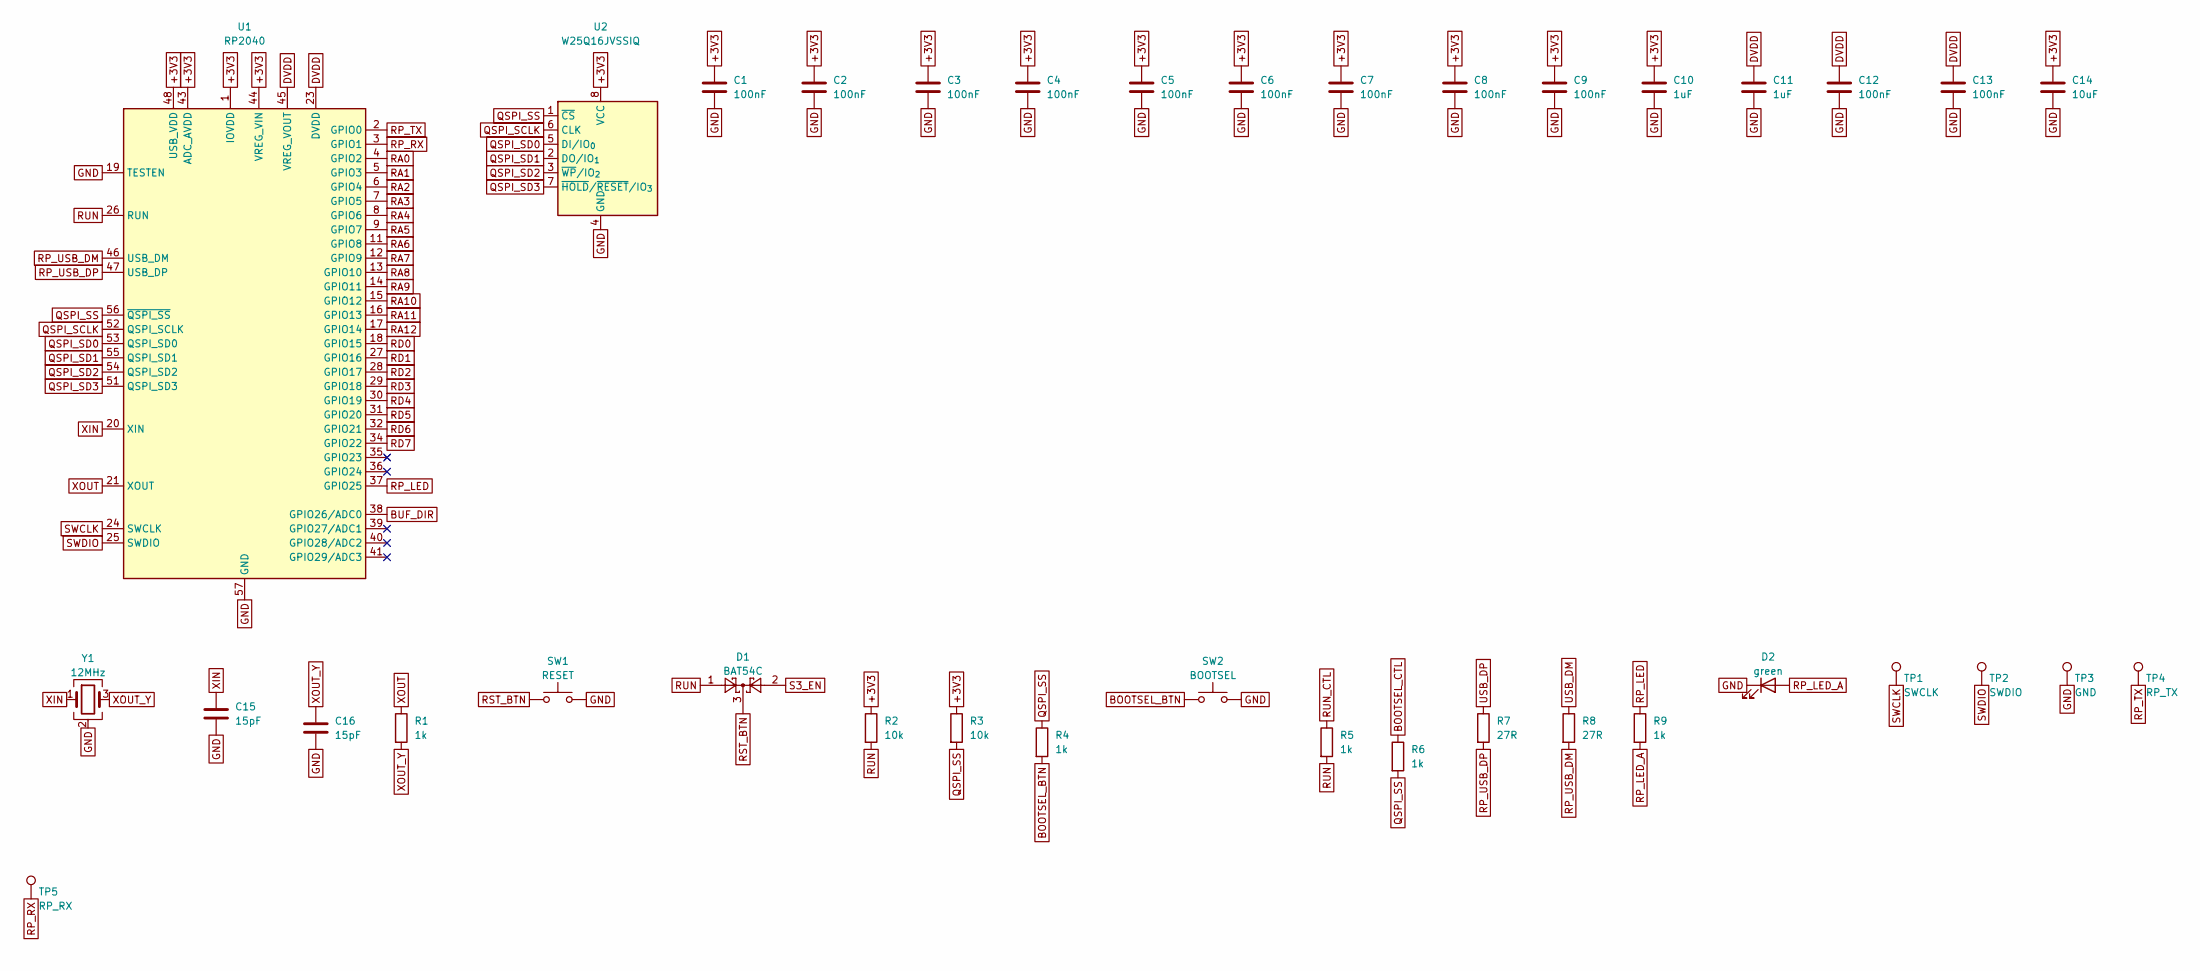
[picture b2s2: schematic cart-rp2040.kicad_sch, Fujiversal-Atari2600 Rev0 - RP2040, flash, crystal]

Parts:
C1, C2, C3, C4, C5, C6, C7, C8, C9, C12, C13: 100nF; C_0603_1608Metric; MPN CC0603KRX7R9BB104; LCSC C14663
C10, C11: 1uF; C_0603_1608Metric; MPN CL10A105KB8NNNC; LCSC C15849
C14: 10uF; C_0603_1608Metric; MPN CL10A106KP8NNNC; LCSC C19702
C15, C16: 15pF; C_0603_1608Metric; MPN CL10C150JB8NNNC; LCSC C1644
D1: BAT54C; SOT-23; MPN BAT54C,215; LCSC C37704
D2: green; LED_0603_1608Metric; MPN KT-0603G; LCSC C12624
R1, R4, R5, R6, R9: 1k; R_0603_1608Metric; MPN 0603WAF1001T5E; LCSC C21190
R2, R3: 10k; R_0603_1608Metric; MPN 0603WAF1002T5E; LCSC C25804
R7, R8: 27R; R_0603_1608Metric; MPN 0603WAF270JT5E; LCSC C25190
SW1: RESET; SW_SPST_TL3342; MPN TL3342F160QG; LCSC C2886898
SW2: BOOTSEL; SW_SPST_TL3342; MPN TL3342F160QG; LCSC C2886898
TP1: SWCLK; TestPoint_Pad_D1.5mm
TP2: SWDIO; TestPoint_Pad_D1.5mm
TP3: GND; TestPoint_Pad_D1.5mm
TP4: RP_TX; TestPoint_Pad_D1.5mm
TP5: RP_RX; TestPoint_Pad_D1.5mm
U1: RP2040; QFN-56-1EP_7x7mm_P0.4mm_EP3.2x3.2mm; MPN RP2040; LCSC C2040
U2: W25Q16JVSSIQ; SOIC-8_5.3x5.3mm_P1.27mm; MPN W25Q16JVSSIQ; LCSC C131025
Y1: 12MHz; Crystal_SMD_3225-4Pin_3.2x2.5mm; MPN ABM8-272-T3; LCSC C20625731

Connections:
+3V3: C1.1, C2.1, C3.1, C4.1, C5.1, C6.1, C7.1, C8.1, C9.1, C10.1, C14.1, R2.1, R3.1, U1.1 (IOVDD), U1.10 (IOVDD), U1.22 (IOVDD), U1.33 (IOVDD), U1.42 (IOVDD), U1.43 (ADC_AVDD), U1.44 (VREG_VIN), U1.48 (USB_VDD), U1.49 (IOVDD), U2.8 (VCC); also elsewhere on the board
BOOTSEL_BTN: R4.2, SW2.1
BOOTSEL_CTL: R6.1; also elsewhere on the board
BUF_DIR: U1.38 (GPIO26/ADC0); also elsewhere on the board
DVDD: C11.1, C12.1, C13.1, U1.23 (DVDD), U1.45 (VREG_VOUT), U1.50 (DVDD)
GND: C1.2, C2.2, C3.2, C4.2, C5.2, C6.2, C7.2, C8.2, C9.2, C10.2, C11.2, C12.2, C13.2, C14.2, C15.2, C16.2, D2.1 (K), SW1.2, SW2.2, TP3.1, U1.19 (TESTEN), U1.57 (GND), U2.4 (GND), Y1.2 (G), Y1.4 (G); also elsewhere on the board
QSPI_SCLK: U1.52 (QSPI_SCLK), U2.6 (CLK)
QSPI_SD0: U1.53 (QSPI_SD0), U2.5 (DI/IO_{0})
QSPI_SD1: U1.55 (QSPI_SD1), U2.2 (DO/IO_{1})
QSPI_SD2: U1.54 (QSPI_SD2), U2.3 (~WP/IO_{2})
QSPI_SD3: U1.51 (QSPI_SD3), U2.7 (~HOLD/~RESET/IO_{3})
QSPI_SS: R3.2, R4.1, R6.2, U1.56 (~QSPI_SS), U2.1 (~CS)
RA0: U1.4 (GPIO2); also elsewhere on the board
RA1: U1.5 (GPIO3); also elsewhere on the board
RA2: U1.6 (GPIO4); also elsewhere on the board
RA3: U1.7 (GPIO5); also elsewhere on the board
RA4: U1.8 (GPIO6); also elsewhere on the board
RA5: U1.9 (GPIO7); also elsewhere on the board
RA6: U1.11 (GPIO8); also elsewhere on the board
RA7: U1.12 (GPIO9); also elsewhere on the board
RA8: U1.13 (GPIO10); also elsewhere on the board
RA9: U1.14 (GPIO11); also elsewhere on the board
RA10: U1.15 (GPIO12); also elsewhere on the board
RA11: U1.16 (GPIO13); also elsewhere on the board
RA12: U1.17 (GPIO14); also elsewhere on the board
RD0: U1.18 (GPIO15); also elsewhere on the board
RD1: U1.27 (GPIO16); also elsewhere on the board
RD2: U1.28 (GPIO17); also elsewhere on the board
RD3: U1.29 (GPIO18); also elsewhere on the board
RD4: U1.30 (GPIO19); also elsewhere on the board
RD5: U1.31 (GPIO20); also elsewhere on the board
RD6: U1.32 (GPIO21); also elsewhere on the board
RD7: U1.34 (GPIO22); also elsewhere on the board
RP_LED: R9.1, U1.37 (GPIO25)
RP_LED_A: D2.2 (A), R9.2
RP_RX: TP5.1, U1.3 (GPIO1)
RP_TX: TP4.1, U1.2 (GPIO0)
RP_USB_DM: R8.2, U1.46 (USB_DM)
RP_USB_DP: R7.2, U1.47 (USB_DP)
RST_BTN: D1.3, SW1.1
RUN: D1.1, R2.2, R5.2, U1.26 (RUN)
RUN_CTL: R5.1; also elsewhere on the board
S3_EN: D1.2; also elsewhere on the board
SWCLK: TP1.1, U1.24 (SWCLK)
SWDIO: TP2.1, U1.25 (SWDIO)
USB_DM: R8.1; also elsewhere on the board
USB_DP: R7.1; also elsewhere on the board
XIN: C15.1, U1.20 (XIN), Y1.1
XOUT: R1.1, U1.21 (XOUT)
XOUT_Y: C16.1, R1.2, Y1.3

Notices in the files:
ATARI-2600/Fujiversal-Atari2600/README.md:
Provenance and license:
CERN-OHL-W-2.0.
- **Circuit blocks:** the ESP32-S3, USB-C/CP2102N/auto-program, microSD,
WS2812 and buck blocks come from `Astrocade/rev0` and `INTV/FujiNet-INTV-Rev0`
in this repository, which derive from the PiNTY CARD (CERN-OHL-W-2.0) and
the ESP32-S3-DevKitC-1 reference design.
- **RP2040 support:** Raspberry Pi "Hardware design with RP2040" minimal
design values (12 MHz ABM8 + 15 pF + 1k, W25Q16, decoupling).
- **Edge geometry and orientation:** the FujiPlusCart prototype in this
repository.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
